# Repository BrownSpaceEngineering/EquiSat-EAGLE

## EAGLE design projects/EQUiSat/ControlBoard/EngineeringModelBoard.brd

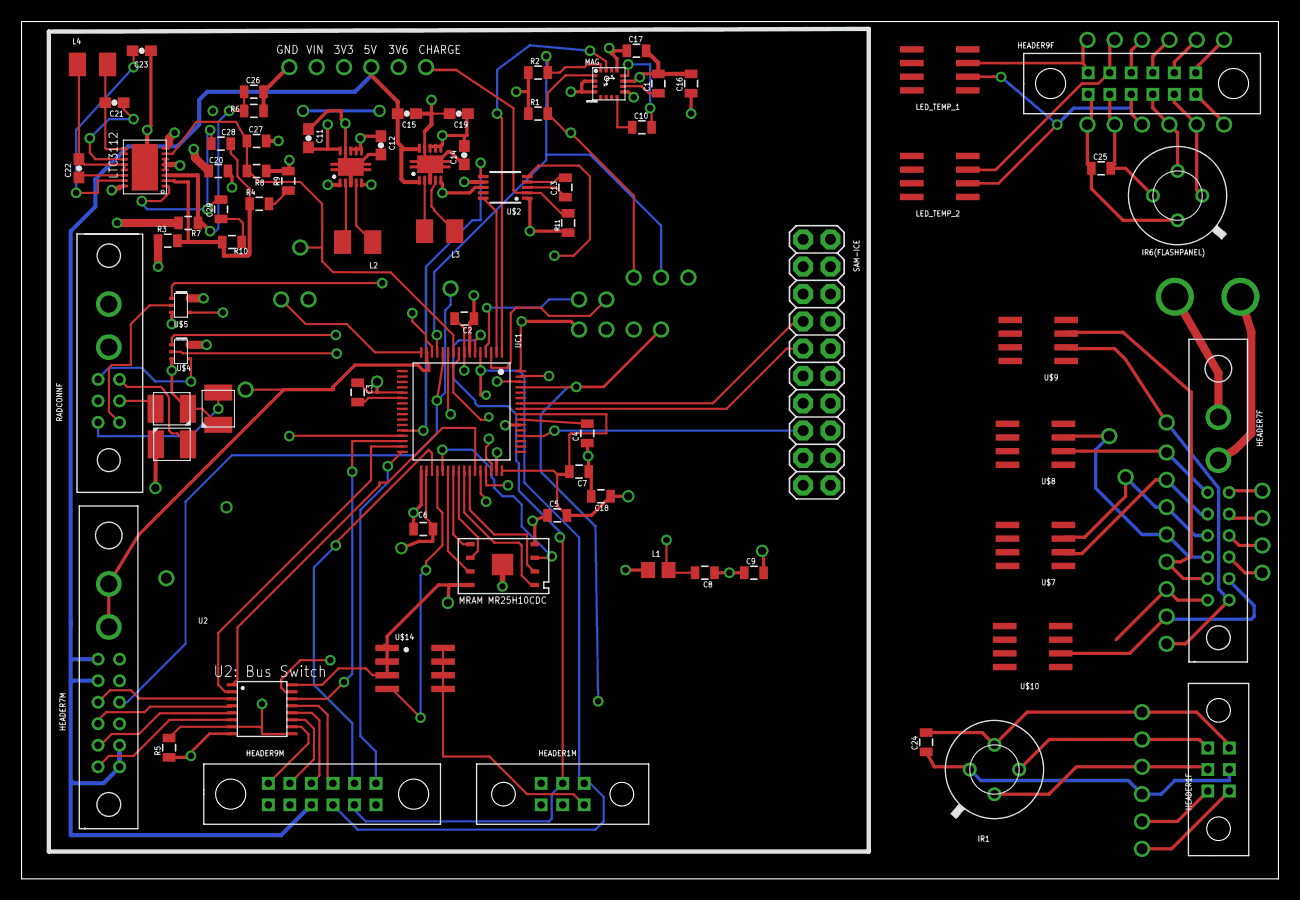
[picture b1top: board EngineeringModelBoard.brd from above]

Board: 4 copper layers, 116.8 x 79.7 mm, 74 parts (0 on the bottom side), 95 nets.

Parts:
63001, 63002: TPS6300X; QFN10_POWERPAD
C1, C13, C16: 4.7uF; 0805
C2, C3, C4, C5, C6, C7, C17, C18: 0.1uF; 0805
C8, C9: 10uF; 0805
C10: .22uF; 0805
C11, C12, C14, C19: 10uF; 0603-CAP
C15: 47uF; 0603-CAP
C20: 47uF; 0805
C21, C22: 0.1uF; 0603-CAP
C23: 1uF; 0603-CAP
C24, C25: 1uF; 0805
C26, C27: 100pF; 0805
C28: 22pF; 0805
C29: 680pF; 0805
HEADER1F, HEADER1M: HARWIN_06; HARWIN_DATAMATE_6
HEADER7F, HEADER7M: HARWIN_DATAMATE_14
HEADER9F, HEADER9M: HARWIN_12; HARWIN_DATAMATE_12
IR1, IR6(FLASHPANEL): MXL90620
L1: BLM21PG221SN1D; R0805
L2: 2.2uH; L3225M
L3: 3.3uH; L3225M
L4: 4.7uH; L3225M
LED_TEMP_1, LED_TEMP_2: AD590-SOIC-8; 8SOIC
MAG: HMC5883L
R1, R2: 2.2K; 0805
R3: 560K; 0805
R4: 150K; 0805
R5: 5.5K; 0805
R6: 47K; 0805
R7: 180K; 0805
R8: 42.2K; 0805
R9: 10K; 0805
R10: 33K; 0805
R11: 0.05R; 0805
RADCONNF: HARWIN_DATAMATE_08
SAM-ICE: 2X10
U2: SOIC16R
U$1: DHD16
U$2: LTC4150; MSOP10
U$3: MRAM; 8PXMO-229
U$4, U$5: 74AUP1G125GW; TSSOP-5
U$7, U$8, U$9, U$10: AD590-SOIC-8; 8SOIC
U$11, U$12, U$13: LT-T673-Q1R2-25-Z; PLCC-2
U$14: POWERPMOS; SO08
UC1: SAMD21JTQFP-64; TQFP-64

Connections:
3V3: 63001.P$1, 63001.P$10, C3.1, C5.2, C6.2, C7.2, C9.2, C11.2, C17.1, C18.1, L1.1, MAG.2, MAG.4, MAG.13, R1.1, R2.1, SAM-ICE.1, U2.P$16, U$3.P8, U$14.1, U$14.2, U$14.3, UC1.P$21, UC1.P$34, UC1.P$48, UC1.P$56
3V3D: HEADER1M.P$4, HEADER9M.P$11, U$14.5, U$14.6, U$14.7, U$14.8
3V3IR: C25.2, HEADER9F.P$11, IR6(FLASHPANEL).VDD
3V6: C20.1, R3.1, R7.1, RADCONNF.P$8, U$1.8, U$4.P$5, U$5.P$5
5V: 63002.P$1, 63002.P$10, C15.2, HEADER7M.P$5, HEADER7M.P$6, HEADER7M.P$7, HEADER7M.P$8, HEADER9M.P$10
CHARGE: R11.2, U$2.2
GND: 63001.P$3, 63001.P$9, 63001.PAD, 63002.P$3, 63002.P$9, 63002.PAD, C1.2, C2.1, C4.1, C5.1, C6.1, C7.1, C8.1, C9.1, C11.1, C12.2, C14.1, C15.1, C16.2, C17.2, C18.2, C19.2, C20.2, C23.1, C26.2, C27.2, HEADER1M.P$5, HEADER9M.P$12, MAG.9, MAG.11, R5.1, R6.1, R8.1, R9.2, RADCONNF.P$7, U2.P$8, U$1.17, U$2.7, U$3.GND, U$3.P4, U$4.P$3, U$5.P$3, U$11.C, U$12.C, U$13.C, UC1.P$7, UC1.P$33, UC1.P$47, UC1.P$54
GNDIR: C25.1, HEADER9F.P$12, IR6(FLASHPANEL).VSS
H1.2: HEADER1F.P$2, IR1.SCL
H1.3: HEADER1F.P$3, IR1.SDA
H1.4: C24.2, HEADER1F.P$4, IR1.VDD
H1.5: C24.1, HEADER1F.P$5, IR1.VSS
H7.1: HEADER7F.P$1, U$10.3
H7.2: HEADER7F.P$2, U$9.3
H7.3: HEADER7F.P$3, U$8.3
H7.4: HEADER7F.P$4, U$7.3
H7.5: HEADER7F.P$5, U$7.2
H7.6: HEADER7F.P$6, U$8.2
H7.7: HEADER7F.P$7, U$9.2
H7.8: HEADER7F.P$8, U$10.2
H9.1: HEADER9F.P$1, LED_TEMP_1.3
H9.2: HEADER9F.P$2, LED_TEMP_2.3
H9.10: HEADER9F.P$10, LED_TEMP_1.2, LED_TEMP_2.2
unnamed: C1.1, MAG.10
unnamed: C21.1, U$1.11
unnamed: C22.1, U$1.14
unnamed: C23.2, U$1.15
unnamed: U$3.P1, UC1.P$41
unnamed: U$3.P2, UC1.P$42
unnamed: U$3.P3, UC1.P$37
unnamed: HEADER9M.P$1, U2.P$10
unnamed: HEADER9M.P$2, U2.P$11
unnamed: HEADER9M.P$3, U2.P$12
unnamed: HEADER9M.P$4, U2.P$13
unnamed: HEADER7M.P$1, U2.P$6
unnamed: HEADER7M.P$2, U2.P$5
unnamed: HEADER7M.P$3, U2.P$4
unnamed: HEADER7M.P$4, U2.P$3
unnamed: U2.P$14, UC1.P$30
unnamed: U2.P$2, UC1.P$31
unnamed: U2.P$1, UC1.P$43
unnamed: U2.P$15, UC1.P$44
unnamed: U$3.P7, UC1.P$38
unnamed: U$3.P6, UC1.P$40
unnamed: C10.1, MAG.8
unnamed: C22.2, L4.1, U$1.12, U$1.13
unnamed: C3.2, UC1.P$22
unnamed: U$3.P5, UC1.P$39
unnamed: C2.2, C8.2, L1.2, UC1.P$8
unnamed: 63002.P$2, L3.2
unnamed: 63002.P$4, L3.1
unnamed: C4.2, UC1.P$55
unnamed: 63001.P$2, L2.2
unnamed: 63001.P$4, L2.1
unnamed: C21.2, L4.2, U$1.9, U$1.10
unnamed: C28.2, R3.2, R4.1, R10.2, U$1.2
unnamed: C13.1, U$2.3
unnamed: C13.2, U$2.4
unnamed: C26.1, R6.2, R7.2, U$1.3
unnamed: C29.1, R10.1
unnamed: C28.1, C29.2, U$1.1
unnamed: U$14.4, UC1.P$36
unnamed: R4.2, R9.1
PA00: MAG.15, UC1.P$1
PA01: U$2.10, UC1.P$2
PA04: MAG.16, R2.2, UC1.P$13
PA05: MAG.1, R1.2, UC1.P$14
PA06: HEADER7M.P$13, HEADER7M.P$14, UC1.P$15
PA12: U$2.5, UC1.P$29
PA15: HEADER9M.P$6, UC1.P$32
PA16: HEADER9M.P$5, UC1.P$35
PA24: U$4.P$2, UC1.P$45
PA25: U$5.P$4, UC1.P$46
PA30: SAM-ICE.9, UC1.P$57
PA31: SAM-ICE.7, UC1.P$58
PB00: R5.2, U2.P$7, U2.P$9, UC1.P$61
PB01: RADCONNF.P$3, UC1.P$62
PB02: U$4.P$1, UC1.P$63
PB03: U$5.P$1, UC1.P$64
PB04: HEADER1M.P$3, HEADER9M.P$9, UC1.P$5
PB05: HEADER1M.P$2, HEADER9M.P$8, UC1.P$6
PB07: C27.1, R8.2, U$1.7, UC1.P$10
PB08: HEADER7M.P$9, UC1.P$11
PB09: HEADER7M.P$10, UC1.P$12
PB15: U$2.6, UC1.P$28
R2: RADCONNF.P$4, U$13.A
R3: RADCONNF.P$5, U$4.P$4
R4: RADCONNF.P$6, U$12.A
R12: RADCONNF.P$1, U$11.A
R14: RADCONNF.P$2, U$5.P$2
RESETN: SAM-ICE.15, UC1.P$52
SCLIR: HEADER9F.P$8, IR6(FLASHPANEL).SCL
SDAIR: HEADER9F.P$9, IR6(FLASHPANEL).SDA
SETC: C10.2, MAG.12
VIN: 63001.P$5, 63001.P$6, 63001.P$7, 63001.P$8, 63002.P$5, 63002.P$6, 63002.P$7, 63002.P$8, C12.1, C14.2, C16.1, C19.1, R11.1, U$1.4, U$1.5, U$1.6, U$1.16, U$2.1, U$2.8

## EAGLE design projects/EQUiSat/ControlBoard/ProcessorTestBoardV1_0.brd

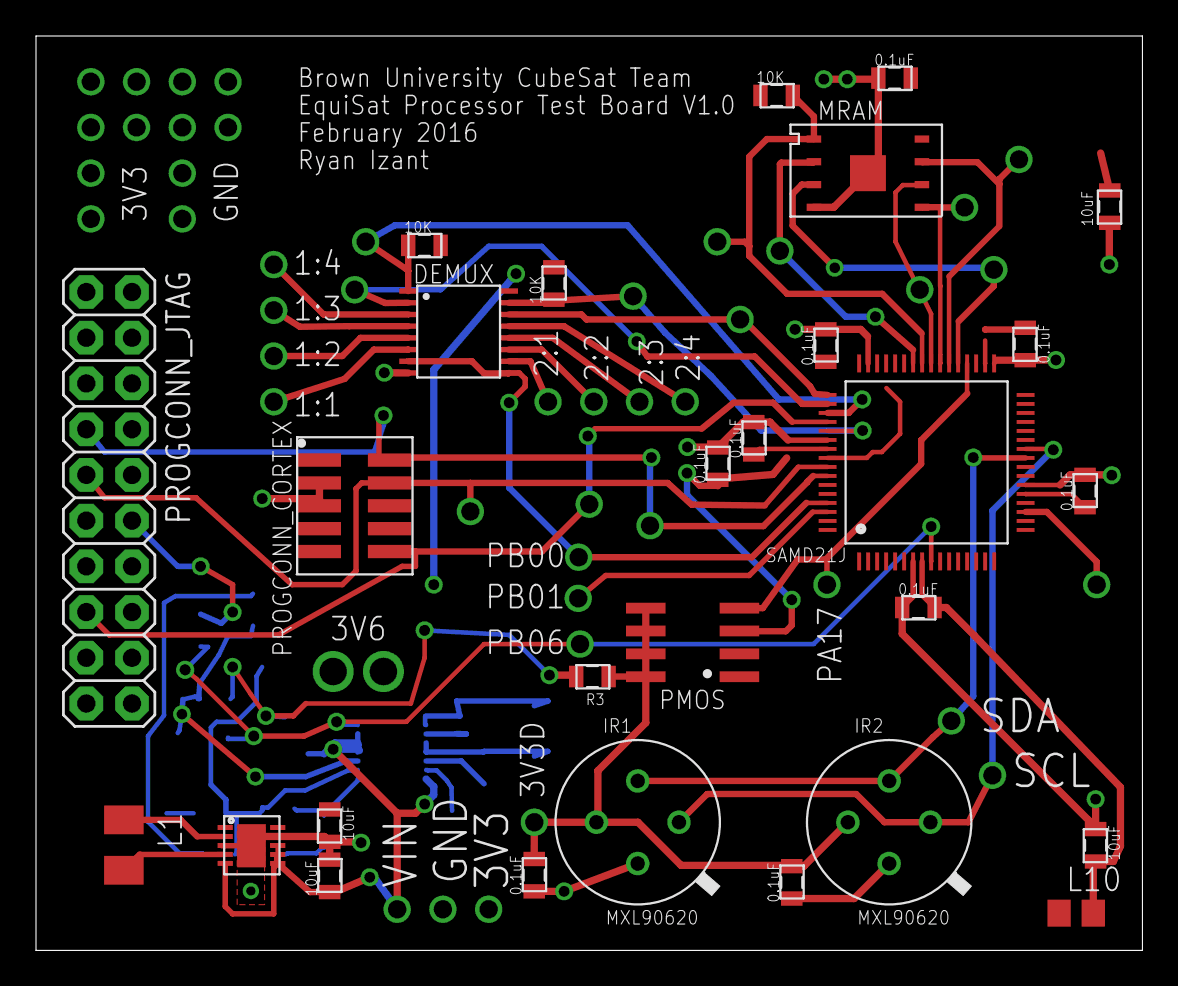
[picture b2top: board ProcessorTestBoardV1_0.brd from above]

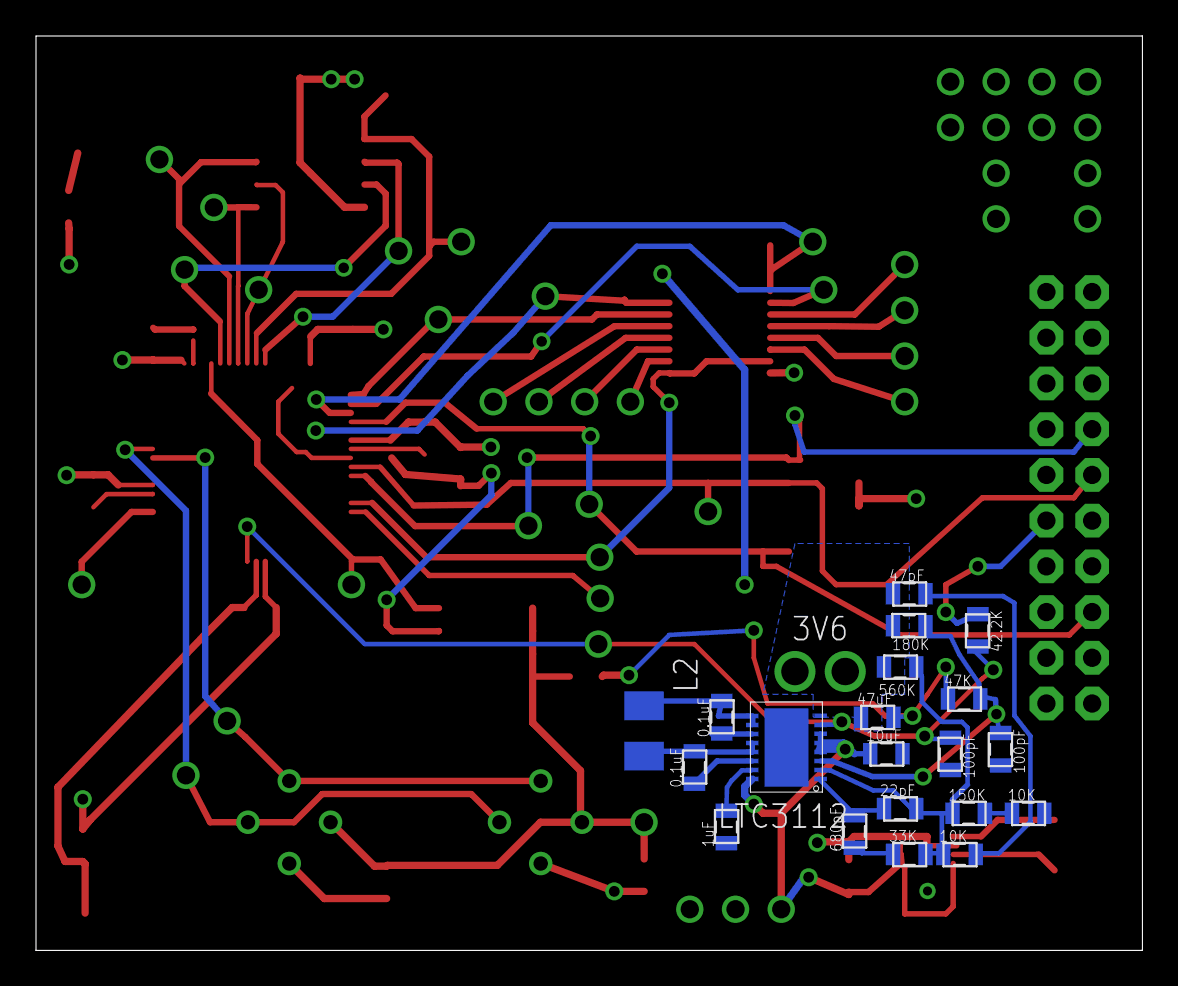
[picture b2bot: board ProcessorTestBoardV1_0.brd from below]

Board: 2 copper layers, 61.5 x 50.8 mm, 48 parts (20 on the bottom side), 38 nets.

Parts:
C1, C2, C5, C10, C16: 10uF; 0805
C3, C4, C6, C7, C8, C9, C11, C12, C13, C21, C22: 0.1uF; 0805
C14: 680pF; 0805
C15: 22pF; 0805
C17, C18: 100pF; 0805
C19: 47uF; 0805
C20: 1uF; 0805
C23: 47pF; 0805
DEMUX: SOIC16R
IR1, IR2: MXL90620
L1: 2.2uH; L3225M
L2: 4.7uH; L3225M
L10: R0805
LTC3112: DHD16
MRAM: 8PXMO-229
PMOS: POWERPMOS; SO08
PROGCONN_CORTEX: HARWIN_ARCHER_10_SMD
PROGCONN_JTAG: 2X10
R1, R2, R3, R4, R5, R12: 10K; 0805
R6: 150K; 0805
R7: 180K; 0805
R8: 33K; 0805
R9: 560K; 0805
R10: 47K; 0805
R11: 42.2K; 0805
SAMD21J: SAMD21JTQFP-64; TQFP-64
TPS63001: TPS6300X; QFN10_POWERPAD

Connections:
3V3: C1.1, C4.1, C5.1, C6.1, C7.1, C8.1, C11.2, DEMUX.P$16, L10.1, MRAM.P8, PMOS.1, PMOS.2, PMOS.3, PROGCONN_CORTEX.1, PROGCONN_JTAG.1, R1.2, R2.2, R4.1, SAMD21J.P$21, SAMD21J.P$34, SAMD21J.P$48, SAMD21J.P$56, TPS63001.P$1, TPS63001.P$10
3V6: C19.1, C23.1, LTC3112.8, R7.2, R9.1
COMP: C14.2, C15.1, LTC3112.1
FB: C15.2, LTC3112.2, R6.1, R8.2, R9.2, R12.1
GND: C1.2, C2.2, C3.2, C4.2, C5.2, C6.2, C7.2, C8.2, C9.1, C10.1, C11.1, C12.1, C13.1, C16.2, C17.2, C18.2, C19.2, C20.1, DEMUX.P$8, IR1.VSS, IR2.VSS, LTC3112.17, MRAM.P4, MRAM.P9, PROGCONN_CORTEX.2, PROGCONN_CORTEX.3, PROGCONN_JTAG.4, PROGCONN_JTAG.6, PROGCONN_JTAG.8, PROGCONN_JTAG.10, PROGCONN_JTAG.12, R3.1, R5.2, R10.1, R11.1, SAMD21J.P$7, SAMD21J.P$22, SAMD21J.P$33, SAMD21J.P$47, SAMD21J.P$54, TPS63001.P$3, TPS63001.P$9, TPS63001.PAD
unnamed: C12.2, C13.2, IR1.VDD, IR2.VDD, PMOS.5, PMOS.6, PMOS.7, PMOS.8, R3.2
unnamed: L1.2, TPS63001.P$4
unnamed: L1.1, TPS63001.P$2
unnamed: C14.1, R8.1
unnamed: C23.2, R12.2
unnamed: R5.1, R6.2
unnamed: C3.1, SAMD21J.P$55
unnamed: C9.2, C10.2, L10.2, SAMD21J.P$8
unnamed: C20.2, LTC3112.15
unnamed: C22.1, LTC3112.14
unnamed: C22.2, L2.2, LTC3112.12, LTC3112.13
unnamed: C21.2, L2.1, LTC3112.9, LTC3112.10
unnamed: C21.1, LTC3112.11
OVP: C17.1, LTC3112.3, R7.1, R10.2
PA17: PMOS.4, SAMD21J.P$36
PA27: DEMUX.P$1, R1.1, SAMD21J.P$51
PA28: DEMUX.P$15, R2.1, SAMD21J.P$53
PA30: PROGCONN_CORTEX.9, PROGCONN_JTAG.9, SAMD21J.P$57
PA31: PROGCONN_CORTEX.10, PROGCONN_JTAG.7, SAMD21J.P$58
PB00: DEMUX.P$7, DEMUX.P$9, SAMD21J.P$61
PB06: C18.1, LTC3112.7, R11.2, SAMD21J.P$9
PB22: DEMUX.P$14, SAMD21J.P$49
PB23: DEMUX.P$2, SAMD21J.P$50
RESETN: PROGCONN_CORTEX.6, PROGCONN_JTAG.15, SAMD21J.P$52
SCK: MRAM.P6, SAMD21J.P$40
SCL: IR1.SCL, IR2.SCL, SAMD21J.P$26
SDA: IR1.SDA, IR2.SDA, SAMD21J.P$25
SI: MRAM.P5, SAMD21J.P$39
SO: MRAM.P2, SAMD21J.P$42
VIN: C2.1, C16.1, LTC3112.4, LTC3112.5, LTC3112.6, LTC3112.16, TPS63001.P$5, TPS63001.P$6, TPS63001.P$7, TPS63001.P$8
~CS: MRAM.P1, R4.2, SAMD21J.P$41
~HOLD: MRAM.P7, SAMD21J.P$38
~WP: MRAM.P3, SAMD21J.P$37

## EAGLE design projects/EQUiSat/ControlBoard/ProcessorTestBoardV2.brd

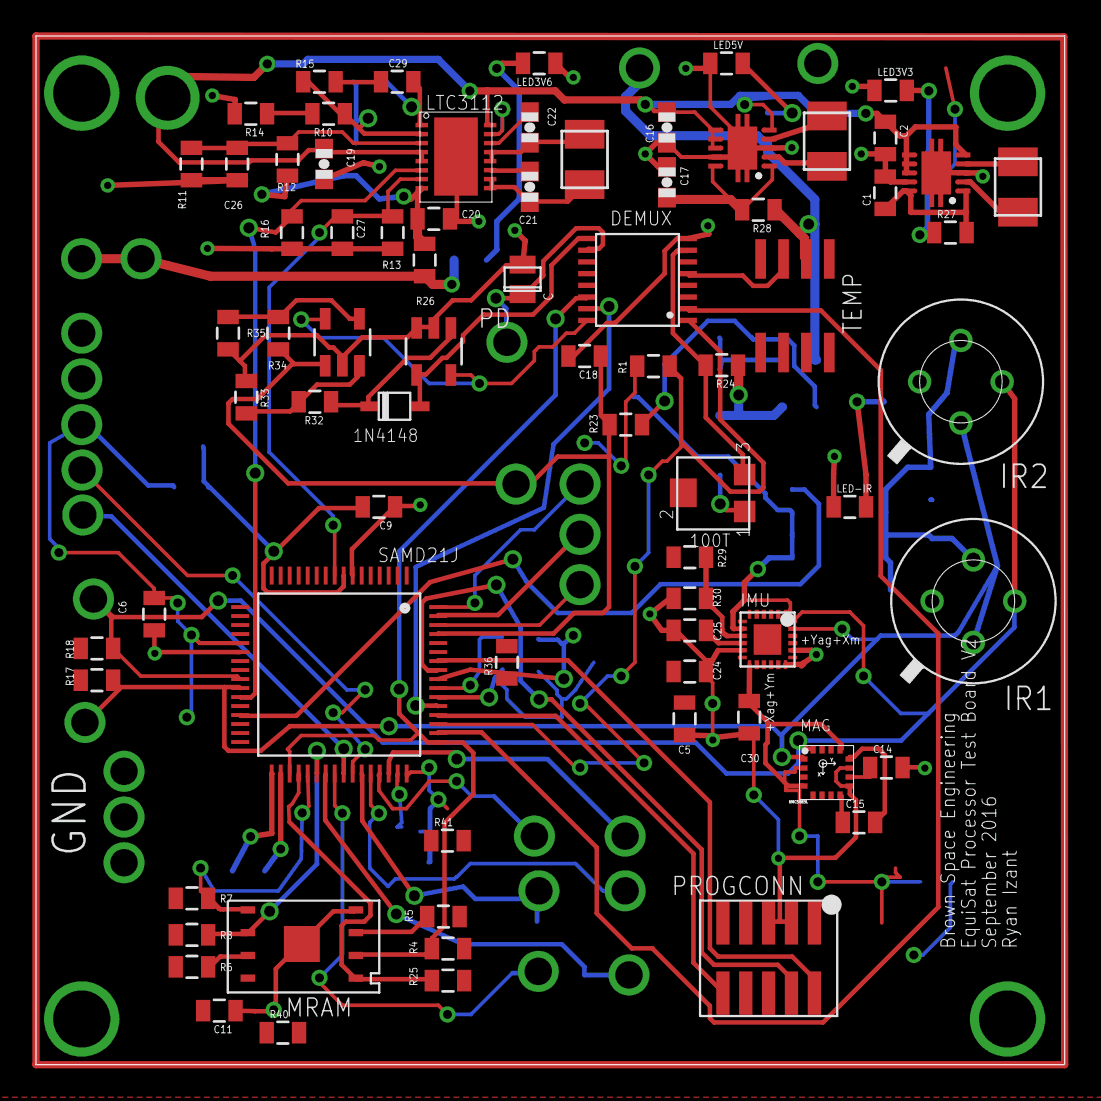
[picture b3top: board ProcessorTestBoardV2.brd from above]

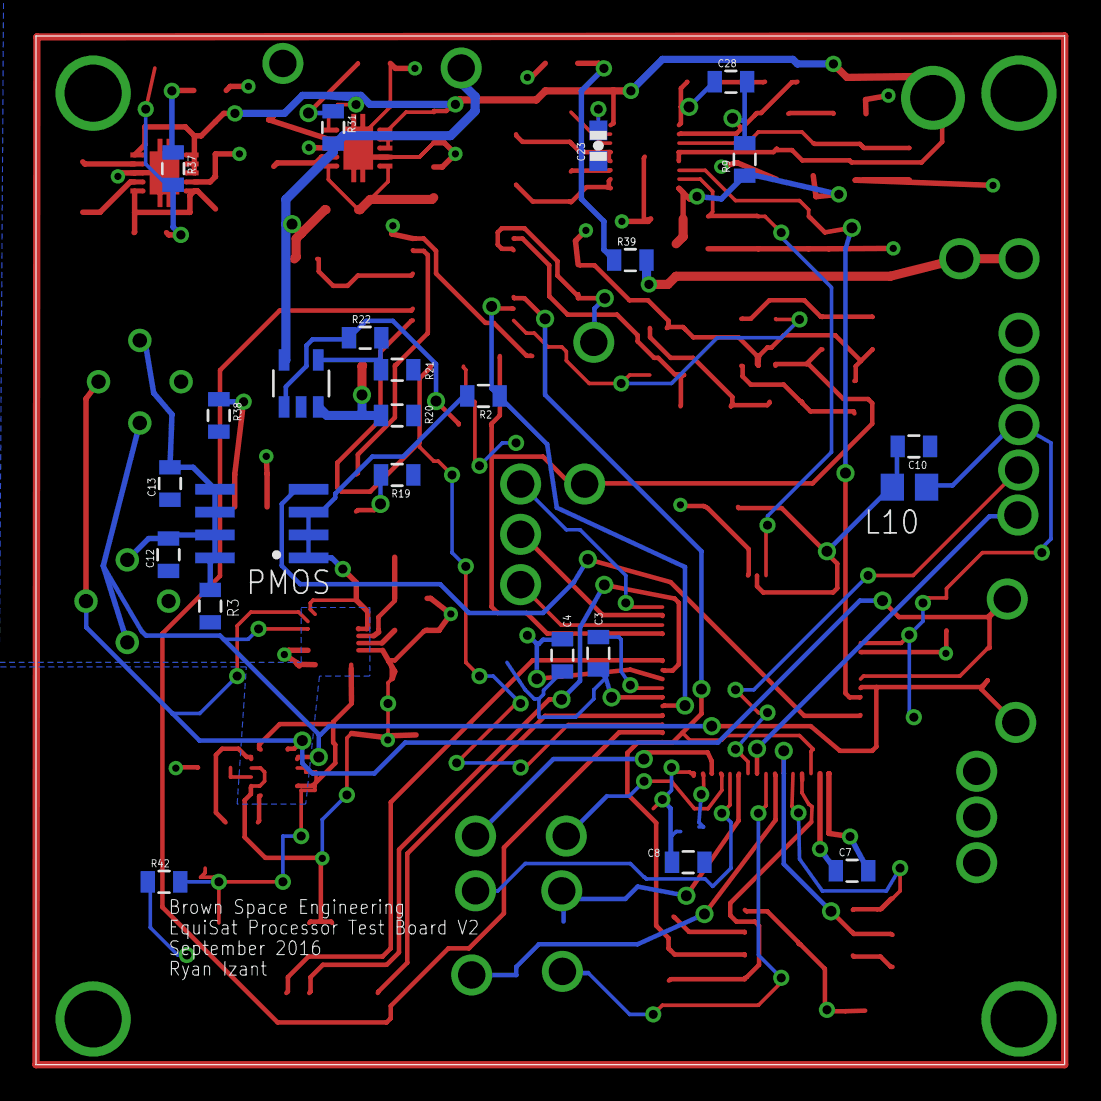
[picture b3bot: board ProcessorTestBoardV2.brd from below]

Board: 2 copper layers, 57.1 x 57.1 mm, 99 parts (24 on the bottom side), 63 nets.

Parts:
1N4148: 1N4148WS; SOD-323F
100T: TRIMPOT-TC33; TC33X-2
63001, 63002: TPS6300X; QFN10_POWERPAD
C1, C2, C5, C10: 10uF; 0805
C3, C4, C6, C7, C8, C9, C11, C12, C13, C18, C24, C25: 0.1uF; 0805
C14: 4.7uF; 0805
C15: .22uF; 0805
C16, C19: 10uF; 0603-CAP
C17: 47uF; 0603-CAP
C20: 47uF; 0805
C21, C22: 0.1uF; 0603-CAP
C23: 1uF; 0603-CAP
C26, C27: 100pF; 0805
C28: 22pF; 0805
C29: 680pF; 0805
C30: 10nF; 0805
DEMUX: SOIC16R
IMU: MPU9250; QFN-24-3X3
IR1, IR2: MXL90620
L1: 2.2uH; L3225M
L3: 3.3uH; L3225M
L4: 4.7uH; L3225M
L10: R0805
LED3V3, LED3V6, LED5V: 0805
LED-IR: 0805
LTC3112: DHD16
MAG: HMC5883L
MRAM: 8PXMO-229
PD: PHOTODETECTOR; PHOTODECTORDEVICE2
PD_A_1, PD_A_2: LT6015; SOT23-5
PMOS: POWERPMOS; SO08
PROGCONN: HARWIN_ARCHER_10_SMD
R1, R2, R3, R14, R21, R24: 10K; 0805
R4, R5, R6, R7, R8, R16, R25, R29, R30: 1K; 0805
R9: 560K; 0805
R10: 150K; 0805
R11: 47K; 0805
R12: 180K; 0805
R13: 42.2K; 0805
R15: 33K; 0805
R17, R18: 2.2K; 0805
R19: 950R; 0805
R20, R22: 60K; 0805
R23: 100K; 0805
R26, R27, R28, R36, R40, R41, R42: 0R; 0805
R31: 560R; 0805
R32, R35: 15K; 0805
R33, R34: 9K; 0805
R37, R38: 250R; 0805
R39: 330R; 0805
SAMD21J: SAMD21JTQFP-64; TQFP-64
TEMP: AD590; 8SOIC
T_AMP: LT6015; SOT23-5

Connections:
3V3: C4.1, C5.1, C6.1, C7.1, C8.1, C11.2, C24.1, C30.1, DEMUX.P$16, IMU.1, IMU.8, IMU.13, L10.1, MAG.2, MAG.4, MAG.13, MRAM.P8, PD_A_1.V+, PD_A_2.V+, PMOS.1, PMOS.2, PMOS.3, PROGCONN.1, R1.2, R2.2, R4.2, R5.2, R6.2, R7.2, R8.2, R17.2, R18.2, R25.2, R27.1, R29.2, R36.1, R36.2, R37.2, R40.1, R40.2, R41.1, R41.2, R42.1, R42.2, SAMD21J.P$21, SAMD21J.P$34, SAMD21J.P$48, SAMD21J.P$56
3V3O: 63001.P$1, 63001.P$10, C1.1, R27.2
3V6: R26.2, R39.2
3V6O: C20.1, LTC3112.8, R9.1, R12.1, R26.1
5V: R28.1, R31.2, TEMP.2, T_AMP.V+
5VO: 63002.P$1, 63002.P$10, C17.2, R28.2
AD0: IMU.9, R29.1, R30.2
GND: 63001.P$3, 63001.P$9, 63001.PAD, 63002.P$3, 63002.P$9, 63002.PAD, C1.2, C2.2, C3.2, C4.2, C5.2, C6.2, C7.2, C8.2, C9.1, C10.1, C11.1, C12.1, C13.1, C14.2, C16.1, C17.1, C18.2, C19.2, C20.2, C23.1, C24.2, C25.2, C26.2, C27.2, C30.2, DEMUX.P$8, IMU.11, IMU.18, IMU.20, IR1.VSS, IR2.VSS, LED3V3.1, LED3V6.1, LED5V.1, LED-IR.1, LTC3112.17, MAG.9, MAG.11, MRAM.P4, MRAM.P9, PD.A, PD_A_1.IN+, PD_A_1.V-, PD_A_2.V-, PROGCONN.2, PROGCONN.3, R3.1, R11.1, R13.1, R14.2, R16.2, R19.1, R20.1, R21.2, R30.1, R33.1, R35.1, SAMD21J.P$7, SAMD21J.P$22, SAMD21J.P$33, SAMD21J.P$47, SAMD21J.P$54, T_AMP.V-
unnamed: C12.2, C13.2, IR1.VDD, IR2.VDD, PMOS.5, PMOS.6, PMOS.7, PMOS.8, R3.2, R38.2
unnamed: 63001.P$4, L1.2
unnamed: 63001.P$2, L1.1
unnamed: C21.1, LTC3112.11
unnamed: C22.1, LTC3112.14
unnamed: C23.2, LTC3112.15
unnamed: C14.1, MAG.10
unnamed: C3.1, SAMD21J.P$55
unnamed: R20.2, R24.1, T_AMP.IN+
unnamed: R22.1, R23.2, T_AMP.OUT
unnamed: R21.1, R22.2, T_AMP.IN-
unnamed: 1N4148.CATHODE, PD_A_1.OUT, R32.1
unnamed: 100T.P$1, R19.2
unnamed: C25.1, IMU.10
unnamed: PD_A_2.IN+, R32.2, R33.2
unnamed: LED-IR.2, R38.1
unnamed: C9.2, C10.2, L10.2, SAMD21J.P$8
unnamed: PD_A_2.IN-, R34.1, R35.2
unnamed: LED3V6.2, R39.1
unnamed: LED5V.2, R31.1
unnamed: LED3V3.2, R37.1
unnamed: C15.1, MAG.8
unnamed: C22.2, L4.1, LTC3112.12, LTC3112.13
unnamed: 63002.P$2, L3.2
unnamed: 63002.P$4, L3.1
unnamed: C21.2, L4.2, LTC3112.9, LTC3112.10
unnamed: C28.2, LTC3112.2, R9.2, R10.1, R15.2
unnamed: C26.1, LTC3112.3, R11.2, R12.2
unnamed: C29.1, R15.1
unnamed: C28.1, C29.2, LTC3112.1
unnamed: R10.2, R14.1
PA12: PMOS.4, SAMD21J.P$29
PA30: PROGCONN.9, SAMD21J.P$57
PA31: PROGCONN.10, SAMD21J.P$58
PB00: C18.1, PD_A_2.OUT, R23.1, R34.2, SAMD21J.P$61
PB06: C27.1, LTC3112.7, R13.2, SAMD21J.P$9
PD-IN: 1N4148.ANODE, DEMUX.P$9, PD_A_1.IN-
PD-OUT: DEMUX.P$10, PD.C
RESETN: PROGCONN.6, SAMD21J.P$52
RUN: LTC3112.6, R16.1, SAMD21J.P$27
S1: DEMUX.P$2, SAMD21J.P$50
SCK: MRAM.P6, R8.1, SAMD21J.P$38
SCL: IMU.23, IR1.SCL, IR2.SCL, MAG.1, R17.1, SAMD21J.P$26
SDA: IMU.24, IR1.SDA, IR2.SDA, MAG.16, R18.1, SAMD21J.P$25
SETC: C15.2, MAG.12
SI: MRAM.P5, R7.1, SAMD21J.P$37
SO: DEMUX.P$14, MRAM.P2, R4.1, SAMD21J.P$35, SAMD21J.P$49
TEMP-IN: 100T.P$3, DEMUX.P$7, R24.2
TEMP-OUT: DEMUX.P$5, TEMP.3
VIN: 63001.P$5, 63001.P$6, 63001.P$7, 63001.P$8, 63002.P$5, 63002.P$6, 63002.P$7, 63002.P$8, C2.1, C16.2, C19.1, LTC3112.4, LTC3112.5, LTC3112.16
~1OE: DEMUX.P$1, R1.1, SAMD21J.P$51
~2OE: DEMUX.P$15, R2.1, SAMD21J.P$53
~CS: MRAM.P1, R25.1, SAMD21J.P$36
~HOLD: MRAM.P7, R6.1
~WP: MRAM.P3, R5.1

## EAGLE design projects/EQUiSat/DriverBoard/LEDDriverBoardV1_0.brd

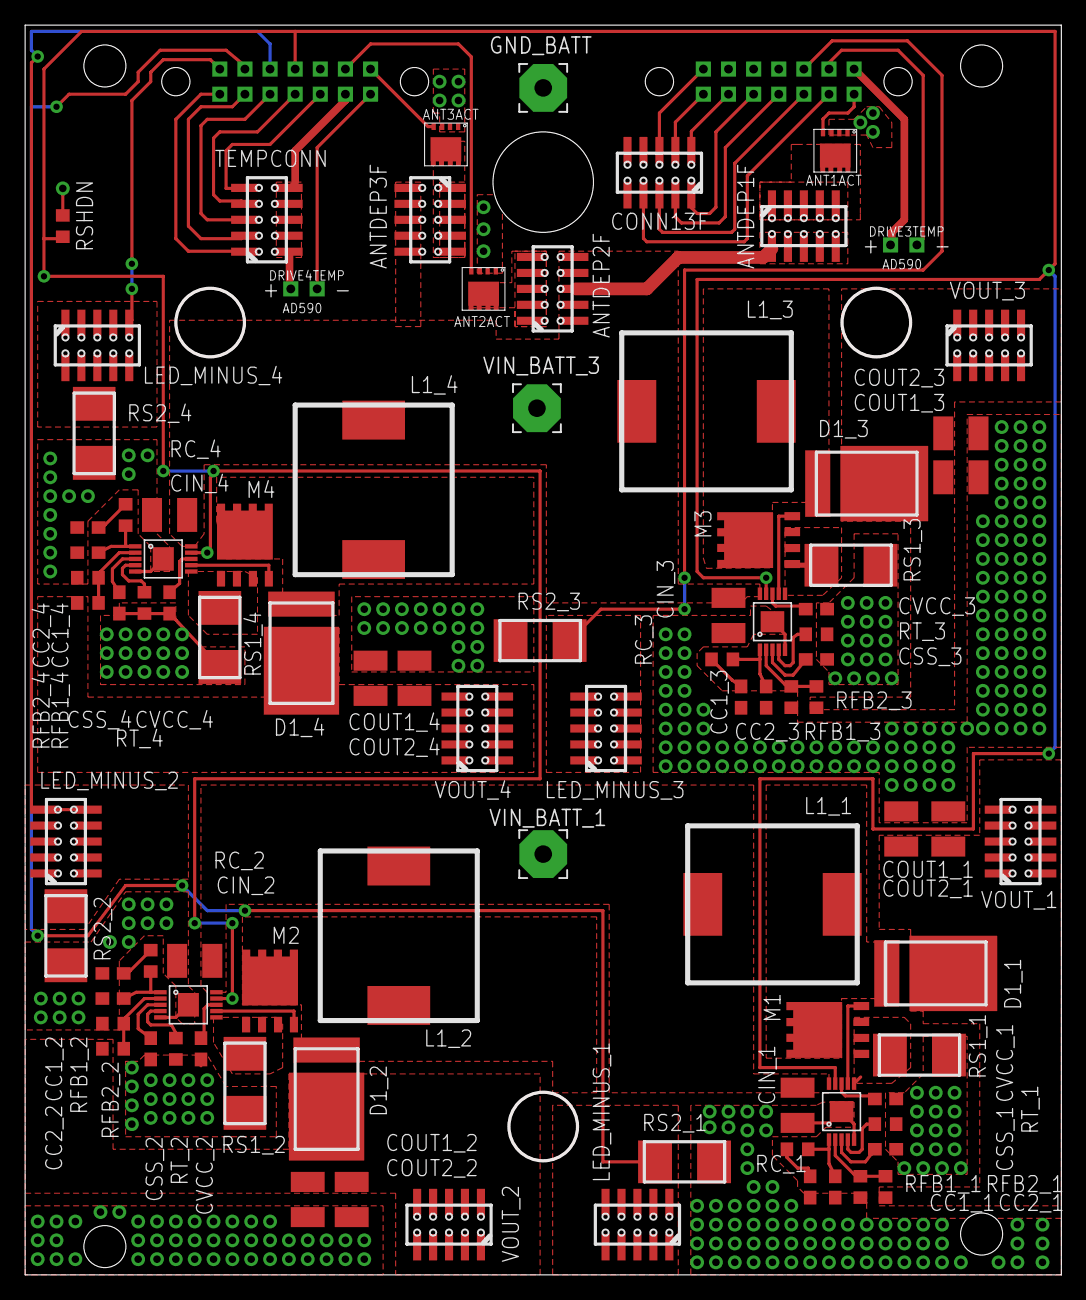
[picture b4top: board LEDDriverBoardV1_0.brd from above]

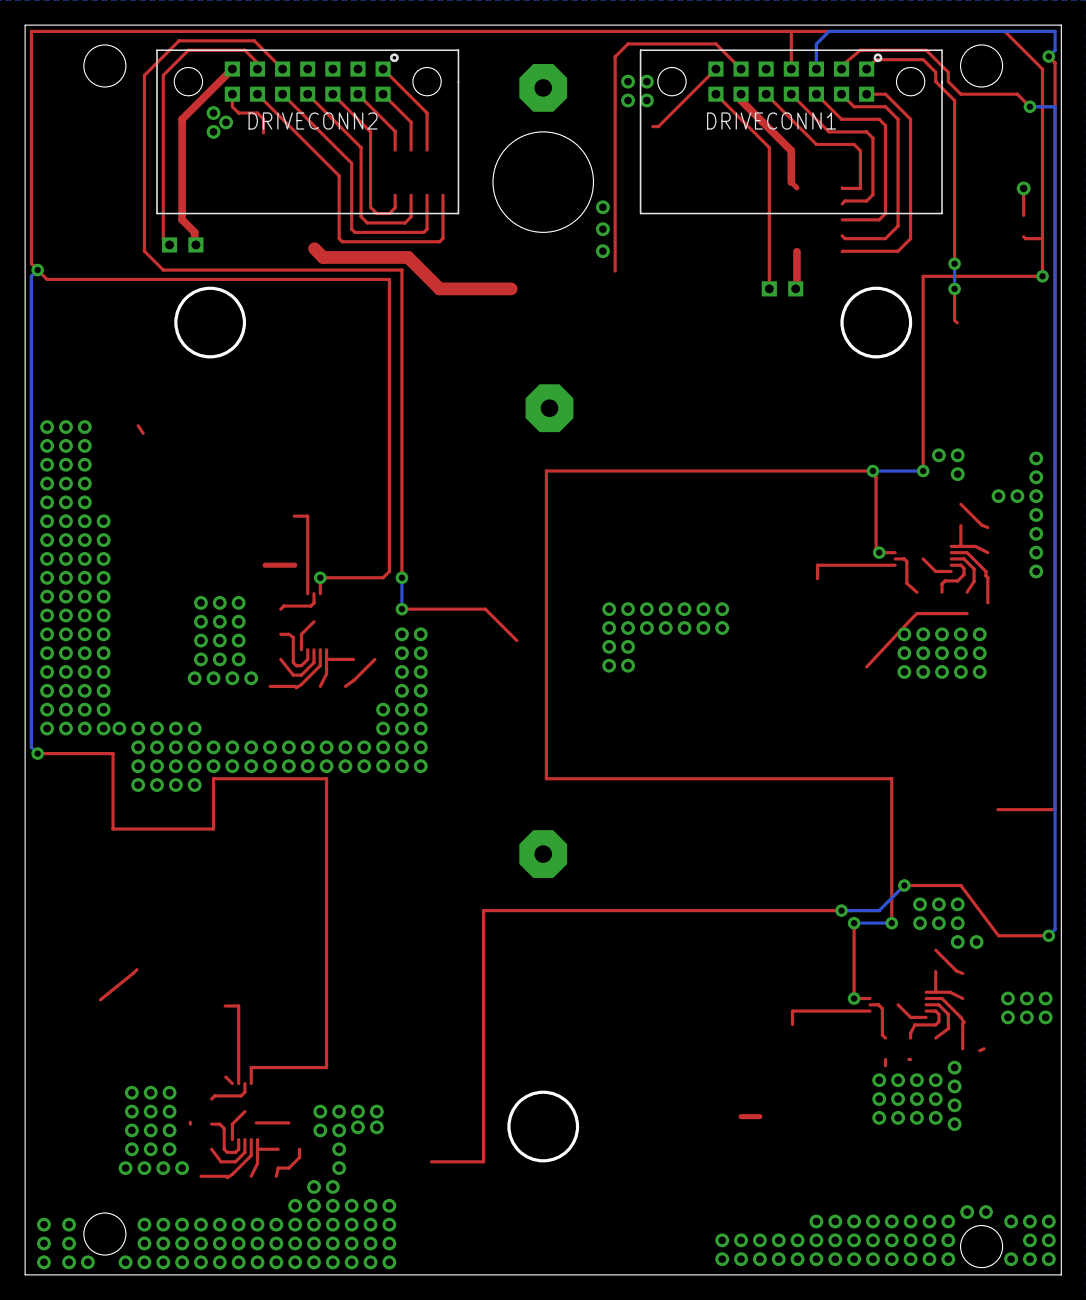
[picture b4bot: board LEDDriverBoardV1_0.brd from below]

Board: 2 copper layers, 82.5 x 99.5 mm, 92 parts (2 on the bottom side), 69 nets.

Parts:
ANT1ACT, ANT2ACT, ANT3ACT: AON7292; DFN3.3X3.3
ANTDEP1F, ANTDEP2F, ANTDEP3F: 10PINFEMALE
CC1_1, CC1_2, CC1_3, CC1_4: C0603
CC2_1, CC2_2, CC2_3, CC2_4: 100p; C0603
CIN_1, CIN_2, CIN_3, CIN_4: 10u; C1210
CONN13F: 10PINFEMALE
COUT1_1, COUT1_2, COUT1_3, COUT1_4, COUT2_1, COUT2_2, COUT2_3, COUT2_4: 10u; C1210
CSS_1, CSS_2, CSS_3, CSS_4: 0.1u; C0603
CVCC_1, CVCC_2, CVCC_3, CVCC_4: 4.7u; C0603
D1_1, D1_2, D1_3, D1_4: SMC(Z5-T)
DRIVE3TEMP, DRIVE4TEMP: AD590-TH; AD590TH
DRIVECONN1, DRIVECONN2: HARWIN_14_HORIZONTAL; HARWIN_DATAMATE_14_HORIZONTAL
GND_BATT: 3,81/1,4
L1_1, L1_2, L1_3, L1_4: 1.5u; SRP1245A
LED_MINUS_1, LED_MINUS_2, LED_MINUS_3, LED_MINUS_4: 10PINFEMALE
M1, M2, M3, M4: POWERFLAT
RC_1, RC_2, RC_3, RC_4: R0603
RFB1_1, RFB1_2, RFB1_3, RFB1_4: 1k; R0603
RFB2_1, RFB2_2, RFB2_3, RFB2_4: 22k; R0603
RS1_1, RS1_2, RS1_3, RS1_4, RS2_1, RS2_2, RS2_3, RS2_4: 3m; ERJMS4S
RSHDN: 1k; R0603
RT_1, RT_2, RT_3, RT_4: 24.3k; R0603
TEMPCONN: 10PINFEMALE
U1, U2, U3, U4: MSOP10
VIN_BATT_1, VIN_BATT_3: 3,81/1,4
VOUT_1, VOUT_2, VOUT_3, VOUT_4: 10PINFEMALE

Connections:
5V_1: DRIVE4TEMP.P$1, DRIVECONN1.P$9, TEMPCONN.6, TEMPCONN.7, TEMPCONN.8, TEMPCONN.9, TEMPCONN.10
5V_2: DRIVE3TEMP.P$1, DRIVECONN2.P$7
FBX_1: RFB1_1.2, RFB2_1.1, U1.P$2
FBX_2: RFB1_2.2, RFB2_2.1, U2.P$2
FBX_3: RFB1_3.2, RFB2_3.1, U3.P$2
FBX_4: RFB1_4.2, RFB2_4.1, U4.P$2
FET_SENSE_1: M1.S1, M1.S2, M1.S3, RS1_1.A, U1.P$6
FET_SENSE_2: M2.S1, M2.S2, M2.S3, RS1_2.A, U2.P$6
FET_SENSE_3: M3.S1, M3.S2, M3.S3, RS1_3.A, U3.P$6
FET_SENSE_4: M4.S1, M4.S2, M4.S3, RS1_4.A, U4.P$6
GATE_1: M1.G, U1.P$7
GATE_2: M2.G, U2.P$7
GATE_3: M3.G, U3.P$7
GATE_4: M4.G, U4.P$7
GND: ANT1ACT.S1, ANT1ACT.S2, ANT1ACT.S3, ANT2ACT.S1, ANT2ACT.S2, ANT2ACT.S3, ANT3ACT.S1, ANT3ACT.S2, ANT3ACT.S3, CC1_1.2, CC1_2.2, CC1_3.2, CC1_4.2, CC2_1.2, CC2_2.2, CC2_3.2, CC2_4.2, CIN_1.2, CIN_2.2, CIN_3.2, CIN_4.2, CONN13F.10, COUT1_1.2, COUT1_2.2, COUT1_3.2, COUT1_4.2, COUT2_1.2, COUT2_2.2, COUT2_3.2, COUT2_4.2, CSS_1.2, CSS_2.2, CSS_3.2, CSS_4.2, CVCC_1.2, CVCC_2.2, CVCC_3.2, CVCC_4.2, DRIVECONN1.P$5, DRIVECONN2.P$13, GND_BATT.1, RFB1_1.1, RFB1_2.1, RFB1_3.1, RFB1_4.1, RS1_1.B, RS1_2.B, RS1_3.B, RS1_4.B, RS2_1.B, RS2_2.B, RS2_3.B, RS2_4.B, RSHDN.1, RT_1.1, RT_2.1, RT_3.1, RT_4.1, U1.P$5, U1.P$11, U2.P$5, U2.P$11, U3.P$5, U3.P$11, U4.P$5, U4.P$11
G_ANT1: ANT1ACT.G, DRIVECONN2.P$8
G_ANT2: ANT2ACT.G, DRIVECONN1.P$6
G_ANT3: ANT3ACT.G, DRIVECONN1.P$7
INTVCC_1: CVCC_1.1, U1.P$8
INTVCC_2: CVCC_2.1, U2.P$8
INTVCC_3: CVCC_3.1, U3.P$8
INTVCC_4: CVCC_4.1, U4.P$8
LDM_1: D1_1.ANODE, L1_1.P$2, M1.D, M1.D5, M1.D6, M1.D7, M1.D8
LDM_2: D1_2.ANODE, L1_2.P$2, M2.D, M2.D5, M2.D6, M2.D7, M2.D8
LDM_3: D1_3.ANODE, L1_3.P$2, M3.D, M3.D5, M3.D6, M3.D7, M3.D8
LDM_4: D1_4.ANODE, L1_4.P$2, M4.D, M4.D5, M4.D6, M4.D7, M4.D8
LED_SENSE_1: DRIVECONN1.P$2, LED_MINUS_1.1, LED_MINUS_1.2, LED_MINUS_1.3, LED_MINUS_1.4, LED_MINUS_1.5, LED_MINUS_1.6, LED_MINUS_1.7, LED_MINUS_1.8, LED_MINUS_1.9, LED_MINUS_1.10, RS2_1.A
LED_SENSE_2: DRIVECONN1.P$3, LED_MINUS_2.1, LED_MINUS_2.2, LED_MINUS_2.3, LED_MINUS_2.4, LED_MINUS_2.5, LED_MINUS_2.6, LED_MINUS_2.7, LED_MINUS_2.8, LED_MINUS_2.9, LED_MINUS_2.10, RS2_2.A
LED_SENSE_3: DRIVECONN2.P$5, LED_MINUS_3.1, LED_MINUS_3.2, LED_MINUS_3.3, LED_MINUS_3.4, LED_MINUS_3.5, LED_MINUS_3.6, LED_MINUS_3.7, LED_MINUS_3.8, LED_MINUS_3.9, LED_MINUS_3.10, RS2_3.A
LED_SENSE_4: DRIVECONN1.P$1, LED_MINUS_4.1, LED_MINUS_4.2, LED_MINUS_4.3, LED_MINUS_4.4, LED_MINUS_4.5, LED_MINUS_4.6, LED_MINUS_4.7, LED_MINUS_4.8, LED_MINUS_4.9, LED_MINUS_4.10, RS2_4.A
unnamed: CC1_2.1, RC_2.1
unnamed: CC1_3.1, RC_3.1
unnamed: CC1_1.1, RC_1.1
unnamed: CC1_4.1, RC_4.1
unnamed: DRIVECONN1.P$11, TEMPCONN.4
unnamed: DRIVECONN1.P$12, TEMPCONN.3
unnamed: DRIVECONN1.P$13, TEMPCONN.2
unnamed: DRIVECONN1.P$14, TEMPCONN.1
unnamed: DRIVECONN1.P$10, TEMPCONN.5
unnamed: DRIVE3TEMP.P$2, DRIVECONN2.P$6
unnamed: DRIVE4TEMP.P$2, DRIVECONN1.P$8
unnamed: CONN13F.4, DRIVECONN2.P$9
unnamed: CONN13F.3, DRIVECONN2.P$10
unnamed: CONN13F.2, DRIVECONN2.P$11
unnamed: CONN13F.1, DRIVECONN2.P$12
unnamed: CONN13F.9, DRIVECONN2.P$14
unnamed: CONN13F.8, DRIVECONN2.P$1
unnamed: ANT3ACT.D1, ANT3ACT.D2, ANT3ACT.D3, ANT3ACT.D4, ANT3ACT.D5, ANTDEP3F.1, ANTDEP3F.2, ANTDEP3F.3, ANTDEP3F.4, ANTDEP3F.5
unnamed: ANT2ACT.D1, ANT2ACT.D2, ANT2ACT.D3, ANT2ACT.D4, ANT2ACT.D5, ANTDEP2F.1, ANTDEP2F.2, ANTDEP2F.3, ANTDEP2F.4, ANTDEP2F.5
unnamed: ANT1ACT.D1, ANT1ACT.D2, ANT1ACT.D3, ANT1ACT.D4, ANT1ACT.D5, ANTDEP1F.1, ANTDEP1F.2, ANTDEP1F.3, ANTDEP1F.4, ANTDEP1F.5
RT_1: RT_1.2, U1.P$4
RT_2: RT_2.2, U2.P$4
RT_3: RT_3.2, U3.P$4
RT_4: RT_4.2, U4.P$4
SHDN_N: DRIVECONN1.P$4, RSHDN.2, U1.P$9, U2.P$9, U3.P$9, U4.P$9
SS_1: CSS_1.1, U1.P$3
SS_2: CSS_2.1, U2.P$3
SS_3: CSS_3.1, U3.P$3
SS_4: CSS_4.1, U4.P$3
VC_1: CC2_1.1, RC_1.2, U1.P$1
VC_2: CC2_2.1, RC_2.2, U2.P$1
VC_3: CC2_3.1, RC_3.2, U3.P$1
VC_4: CC2_4.1, RC_4.2, U4.P$1
VIN_BATT_1: CIN_1.1, CIN_2.1, L1_1.P$1, L1_2.P$1, U1.P$10, U2.P$10, VIN_BATT_1.1
VIN_BATT_3: ANTDEP1F.6, ANTDEP1F.7, ANTDEP1F.8, ANTDEP1F.9, ANTDEP1F.10, ANTDEP2F.6, ANTDEP2F.7, ANTDEP2F.8, ANTDEP2F.9, ANTDEP2F.10, ANTDEP3F.6, ANTDEP3F.7, ANTDEP3F.8, ANTDEP3F.9, ANTDEP3F.10, CIN_3.1, CIN_4.1, L1_3.P$1, L1_4.P$1, U3.P$10, U4.P$10, VIN_BATT_3.1
VOUT_1: COUT1_1.1, COUT2_1.1, D1_1.CATHODE, RFB2_1.2, VOUT_1.1, VOUT_1.2, VOUT_1.3, VOUT_1.4, VOUT_1.5, VOUT_1.6, VOUT_1.7, VOUT_1.8, VOUT_1.9, VOUT_1.10
VOUT_2: COUT1_2.1, COUT2_2.1, D1_2.CATHODE, RFB2_2.2, VOUT_2.1, VOUT_2.2, VOUT_2.3, VOUT_2.4, VOUT_2.5, VOUT_2.6, VOUT_2.7, VOUT_2.8, VOUT_2.9, VOUT_2.10
VOUT_3: COUT1_3.1, COUT2_3.1, D1_3.CATHODE, RFB2_3.2, VOUT_3.1, VOUT_3.2, VOUT_3.3, VOUT_3.4, VOUT_3.5, VOUT_3.6, VOUT_3.7, VOUT_3.8, VOUT_3.9, VOUT_3.10
VOUT_4: COUT1_4.1, COUT2_4.1, D1_4.CATHODE, RFB2_4.2, VOUT_4.1, VOUT_4.2, VOUT_4.3, VOUT_4.4, VOUT_4.5, VOUT_4.6, VOUT_4.7, VOUT_4.8, VOUT_4.9, VOUT_4.10
